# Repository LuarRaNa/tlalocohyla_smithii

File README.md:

# Tlalocohyla Smithii

These keyboards were my inspiration:

```mermaid
graph TD;
    Keyboards-->A;
    Keyboards-->C;
    A[Horizon] --> B[ChocV];
    C[Hummingbird] --> D[Rufous];
    B --> E[Smithii];
    D --> E[Smithii];
    click A "https://github.com/skarrmann/horizon" "Go to";
    click B "https://github.com/brickbots/chocV" "Go to";
    click C "https://github.com/PJE66/hummingbird" "Go to";
    click D "https://github.com/jcmkk3/trochilidae" "Go to";
```

In a nutshell...
- I really liked the Horizon/ChocV construction design and the end result of a low-profile case, just PCBs, nuts and screws.
- And I also liked the Hummingbird/Rufous 30-key layout and the awesome Xiao BLE to package a full Bluetooth keyboard powered by ZMK firmware.

<details>
<summary>How it looks like?</summary>

</details>

## BOM - WIP
|Qty|Materials|-|
|-|-|-|
|1|Main PCB|-|
|1|Bottom PCB|-|
|1|Top PCB|-|
|30|1N4148 SOD-123 diodes|-|
|30|Keycaps|-|
|30|Choc Switches V1|-|
|2|Pogo pin 5mm|[AliExpress (DHYXDD Store) - 5mm](https://es.aliexpress.com/item/1005004016701633.html)|
|1|Machined pin header|-|
|1|Seeeduino Xiao BLE|-|
|1|Li-Po battery (Optional)|I used 501240|
|5|M2 6mm Screws|[AliExpress (wuhushiyu) - 200PCS-M2 Mix - Black/White](https://www.aliexpress.com/item/32862529967.html)|
|5|M2 Nuts|See &uarr;|
|3|M2 6mm Male-Female standoffs|See &uarr;|
|1|JST-PH  male right angle connector (Optional)|-|
|1|Tact Switch (Optional, Reset)|-|
|1|MSK-12C02 (Optional, Power cut-off)|-|
|5~6|2mm tall rubber bumpons|-|

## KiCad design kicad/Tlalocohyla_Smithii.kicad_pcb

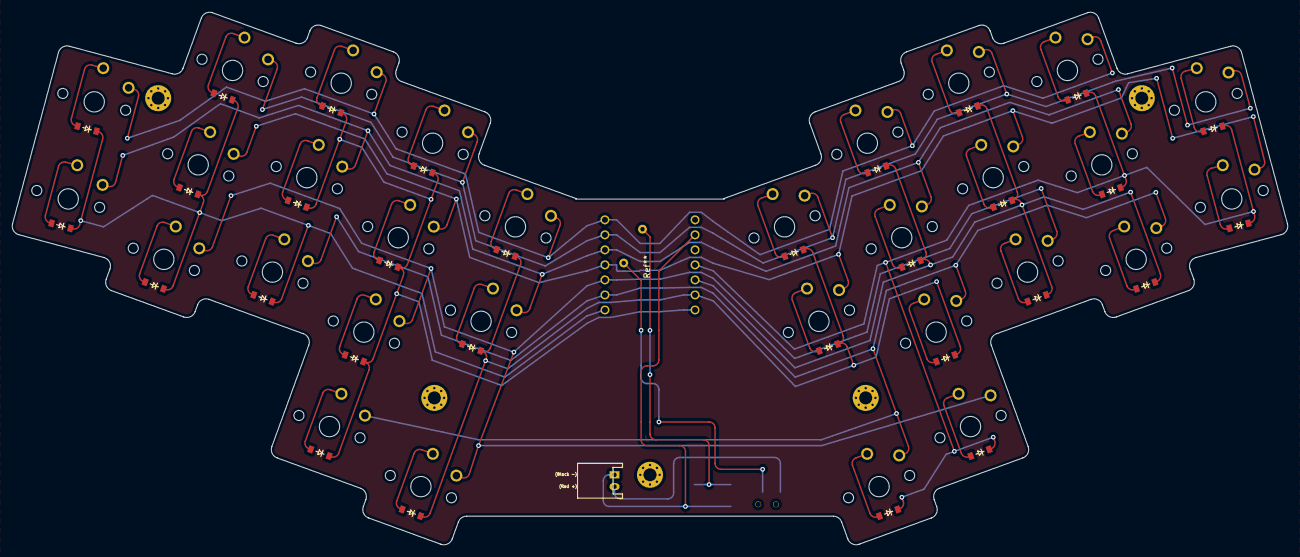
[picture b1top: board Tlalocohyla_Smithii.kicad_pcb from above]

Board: 2 copper layers, 215.7 x 90.0 mm, 69 parts (0 on the bottom side), 45 nets.

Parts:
B1: SW_TACT_ALPS_SKQGABE010
D1, D2, D3, D4, D5, D6, D7, D8, D9, D10, D11, D12, D13, D14, D15, D16, D17, D18, D19, D20, D21, D22, D23, D24, D25, D26, D27, D28, D29, D30: ComboDiode
H**: Mounting_hole
H**#2, H**#3, H**#4, H**#5: Mounting_hole
JST1: JST_PH_S2B-PH-K_02x2.00mm_Angled
Ref**: Val**; Xiao BLE pogo pins
S1, S2, S3, S4, S5, S6, S7, S8, S9, S10, S11, S12, S13, S14, S15, S16, S17, S18, S19, S20, S21, S22, S23, S24, S25, S26, S27, S28, S29, S30: PG1350
T1: SPDT_C128955

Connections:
Bplus: Ref**.15, T1.2
GND_XIAO: B1.2, JST1.1, Ref**.13
JSTplus: JST1.2, T1.1
P0: Ref**.1, S2.1, S8.1, S13.1, S20.1, S26.1
P1: Ref**.2, S5.1, S11.1, S17.1, S23.1, S28.1
P2: Ref**.3, S1.1, S7.1, S12.1, S19.1, S25.1
P3: Ref**.4, S4.1, S10.1, S16.1, S22.1, S27.1
P4: Ref**.5, S3.1, S9.1, S15.1, S21.1, S29.1
P5: Ref**.6, S6.1, S14.1, S18.1, S24.1, S30.1
P6: D1.1, D2.1, D3.1, D4.1, D5.1, D6.1, Ref**.7
P7: D7.1, D8.1, D9.1, D10.1, D11.1, D14.1, Ref**.8
P8: D12.1, D13.1, D15.1, D24.1, D27.1, D28.1, Ref**.9
P9: D18.1, D21.1, D22.1, D23.1, D25.1, D26.1, Ref**.10
P10: D16.1, D17.1, D19.1, D20.1, D29.1, D30.1, Ref**.11
RST_XIAO: B1.1, Ref**.16
index_bottom: D9.2, S9.2
index_home: D10.2, S10.2
index_top: D11.2, S11.2
inner_home: D12.2, S12.2
inner_top: D13.2, S13.2
middle_bottom: D6.2, S6.2
middle_home: D7.2, S7.2
middle_top: D8.2, S8.2
mirror_index_bottom: D24.2, S24.2
mirror_index_home: D25.2, S25.2
mirror_index_top: D26.2, S26.2
mirror_inner_home: D27.2, S27.2
mirror_inner_top: D28.2, S28.2
mirror_middle_bottom: D21.2, S21.2
mirror_middle_home: D22.2, S22.2
mirror_middle_top: D23.2, S23.2
mirror_pinky_home: D16.2, S16.2
mirror_pinky_top: D17.2, S17.2
mirror_reachy_default: D30.2, S30.2
mirror_ring_bottom: D18.2, S18.2
mirror_ring_home: D19.2, S19.2
mirror_ring_top: D20.2, S20.2
mirror_tucky_default: D29.2, S29.2
pinky_home: D1.2, S1.2
pinky_top: D2.2, S2.2
reachy_default: D15.2, S15.2
ring_bottom: D3.2, S3.2
ring_home: D4.2, S4.2
ring_top: D5.2, S5.2
tucky_default: D14.2, S14.2

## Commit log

2022-03-12 Initial commit
    Add ergogen file.
2022-03-12 Add kicad_pcb and footprints
2022-03-17 Add filled zone
2022-05-03 Change Xiao footprint
    Reset and Battery plus
2022-07-25 Adjust tracks
2022-07-25 New Xiao BLE (pogo pins) footprint
2022-07-26 Add library footprints
2022-07-26 Update battery and bottom PCB
2022-11-13 Update battery and bottom PCB
    - Adjusments
    - New frog footprint
2022-11-13 Add gerber files
2022-11-14 Update mermaid diagram
2022-12-19 Update README.md
    Add BOM
